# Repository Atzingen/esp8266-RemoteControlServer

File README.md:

# esp8266-RemoteControlServer

#### Software and Electronics (PCB and schematic) for a esp8266-12e board remote control

This is a project (both software and hardware) for an web controlled IR (infra Read) emitter using an esp8266 microcontroller.

The software in esp8266 is a webserver that serves an single-page web interface (figure 2) with the control buttons for the desired IF device (TV, AC, or other), using html and bootstrap css. The esp8266 webserver also receives GET requests from each specific button. Button pressed requests are done asynchronous using ajax with the help of Jquery mobile library.

The electronic board pcb is composed of the eso8266 model 12-e with the bare minimal components for use, a Infra Read LED emitter and a linear power regulator to enable the use of 5V power supplies. The schematics are available in eagle files in the "pcb" folder and printable pdf files fot pcb etching.

Photos
=========

Figure 1 - Interface provided by the esp8266 webserver.

Figure 2 - Assembled board. 4.5 to 9V input.

Authors
=========

Gustavo Voltani von Atzingen

References
=========

1- https://github.com/esp8266/Arduino

2- http://bbs.espressif.com/

3- http://www.esp8266.com/

4- https://github.com/markszabo/IRremoteESP8266

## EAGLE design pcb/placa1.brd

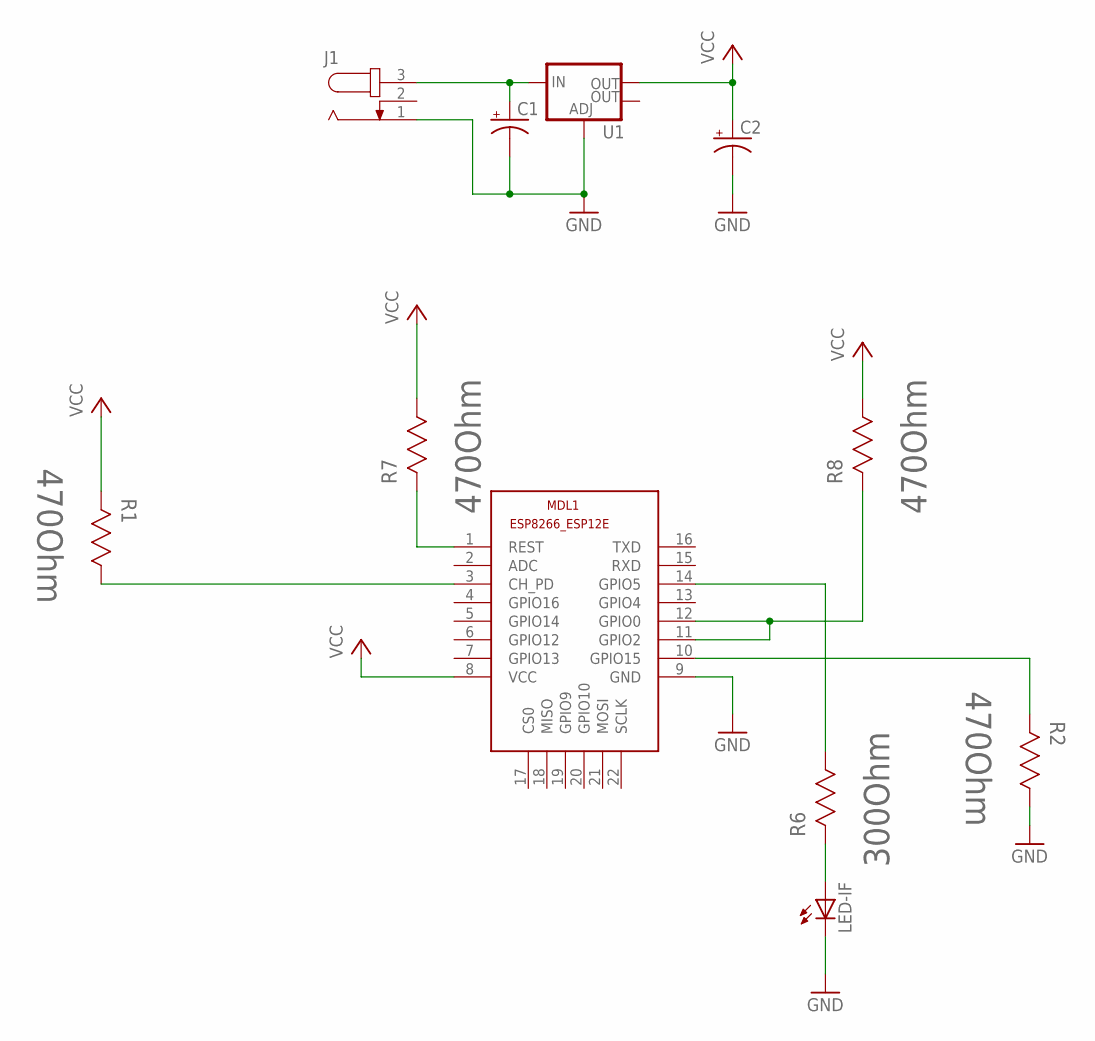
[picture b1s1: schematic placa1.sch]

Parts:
C1, C2: CAP_POLC; PANASONIC_C
J1: JACK-PLUG0; SPC4077
LED-IF: LED5MM
MDL1: ESP8266-12EESP8266-ESP12E; ESP8266-ESP12E
R1, R2, R7, R8: 470Ohm; RESC2013X65N
R6: 300Ohm; RESC2013X65N
U1: V_REG_LM1117SOT223; SOT223

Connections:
GND: C1.-, C2.-, J1.1, LED-IF.K (C), MDL1.9 (GND), R2.1 (R1), U1.1 (ADJ)
unnamed: MDL1.3 (CH_PD), R1.1 (R1)
unnamed: MDL1.10 (GPIO15), R2.2 (R2)
unnamed: MDL1.11 (GPIO2), MDL1.12 (GPIO0), R8.2 (R2)
unnamed: MDL1.1 (REST), R7.2 (R2)
unnamed: MDL1.14 (GPIO5), R6.1 (R1)
unnamed: C1.+, J1.3, U1.3 (IN)
unnamed: LED-IF.A, R6.2 (R2)
VCC: C2.+, MDL1.8 (VCC), R1.2 (R2), R7.1 (R1), R8.1 (R1), U1.2 (OUT)

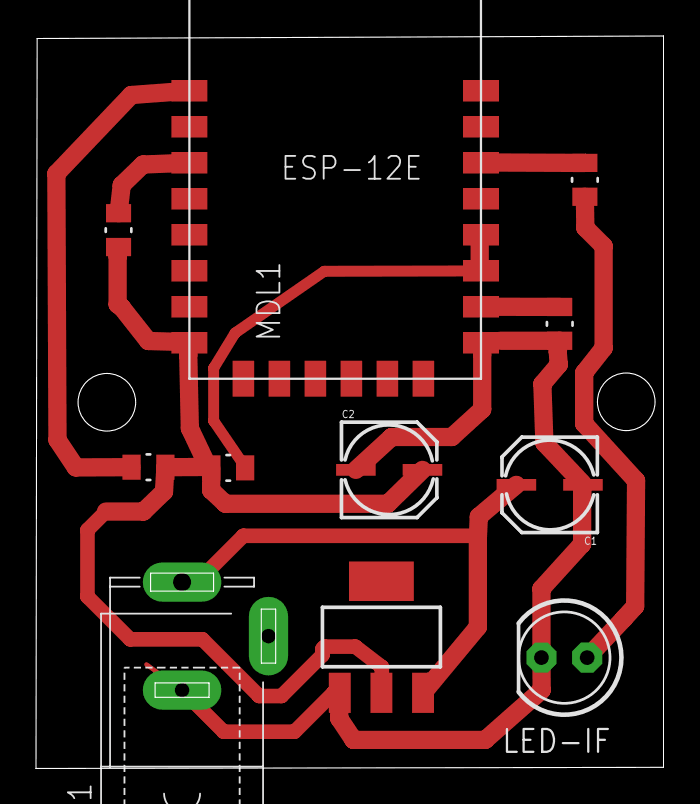
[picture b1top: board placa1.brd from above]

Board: 2 copper layers, 34.9 x 40.7 mm, 11 parts (0 on the bottom side), 9 nets.

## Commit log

2016-03-16 first update
2016-03-16 Fotos adicionadas
2016-03-17 readme update

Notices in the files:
parts and their libraries:
SparkFun-Capacitors: Licensing: Creative Commons ShareAlike 4.0 International - https://creativecommons.org/licenses/by-sa/4.0
